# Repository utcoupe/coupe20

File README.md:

Coupe de France de Robotique 2020 - UTCoupe
=======
|master|devel|
|------|-----|
|  |  |

# Configuration

First clone the repo to your PC :
```
git clone git@github.com:utcoupe/coupe20.git
```

### Development environment configuration

An automated installation script is available. Go in the 'coupe20' folder and launch :
```
./scripts/install_utcoupe_setup.sh 
```

If it is your first installation, answer "y" to all questions.

### Compile the system

The whole system relies on ROS (http://www.ros.org/). Therefore you need to compile the system after having fetched it :
```
cd coupe20/ros_ws
catkin_make
```

### Source the system

Do not forget to source it !
If you are using bash : 
'''
source devel/setup.bash
'''

If you are using zsh : 
'''
source devel/setup.zsh
'''

You can add the source command with the absolute path to setup.bash in ~/.bashrc (or ~/.zshrc) to automate this process.

# Project guidelines

Here are some rules we follow to keep project consistency :

### Git

- Create git branches of format `namespace/package` for ROS packages (e.g. `ai/scheduler`, `memory/map`, etc).

### ROS packages

- Create ROS packages of format `namespace_package` (for alphabetic order sorting purposes)

- Create `topics`/`services`/`actions` in the format `/namespace/package/server_name` if they can be accessed by extern packages (WARNING : with `/` at the beginning to create an absolute name), `server_name` if they are only intern.

- Name definition files `.msg`/`.srv`/`.action` in PascalCase (e.g. `GetValues.srv`) and variables inside in lower case(format `var_name`).

### Python

- PEP8 : 4 indentation spaces (no tabs).

### Data

- Distance units in m, stored as `float32`.

- When describing a shape (circle, line, rectangle, point...), give the position relative to the center of the shape unless it is absolutely necessary.  For example, do not give the corner of a rectangle.

# Webclient

To install the webclient dependency :
```
cd webclient
npm install --only=prod
```

To launch the webclient :
```
npm start
```

Make sure the ROS node `rosbridge_server` starts right.

The webclient can be launched from the robot or a PC connected to the embedded computer (e.g. Raspberry or Lattepanda).

If the server is launched on the robot, go to `http://<ip_of_embedded_computer>:8080`.

Else, go to [http://localhost:8080](http://localhost:8080) and check if the client connects to the robot IP in the parameters.

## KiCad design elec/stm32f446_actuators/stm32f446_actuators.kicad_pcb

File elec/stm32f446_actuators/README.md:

# STM32F446re - Actuators

[Interactive BOM](http://htmlpreview.github.io/?https://github.com/utcoupe/coupe20/blob/elec/elec/stm32f446_actuators/bom/ibom.html)

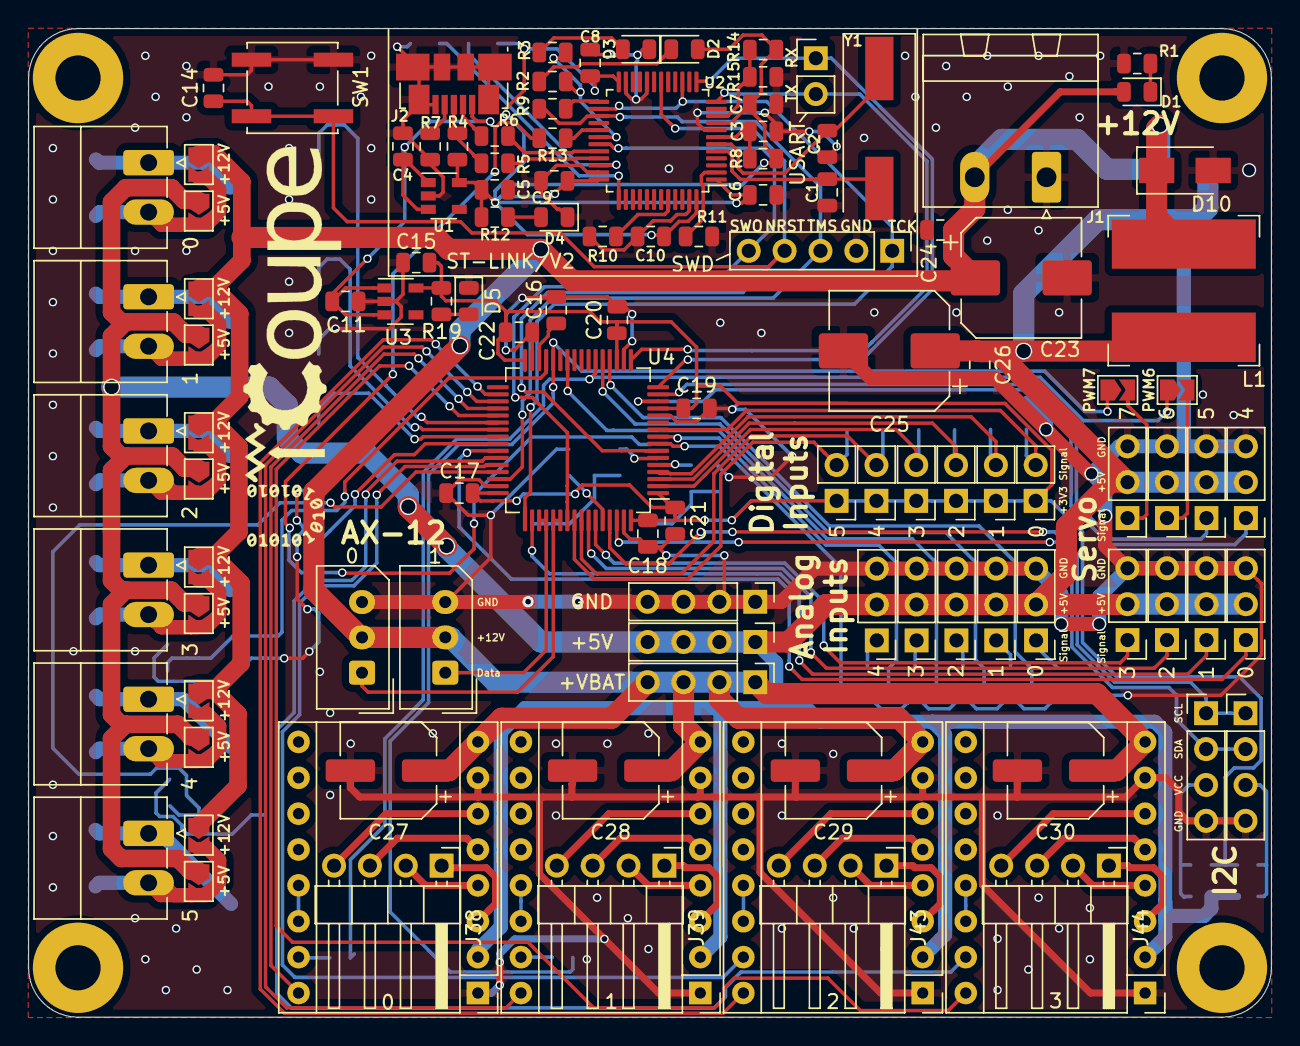
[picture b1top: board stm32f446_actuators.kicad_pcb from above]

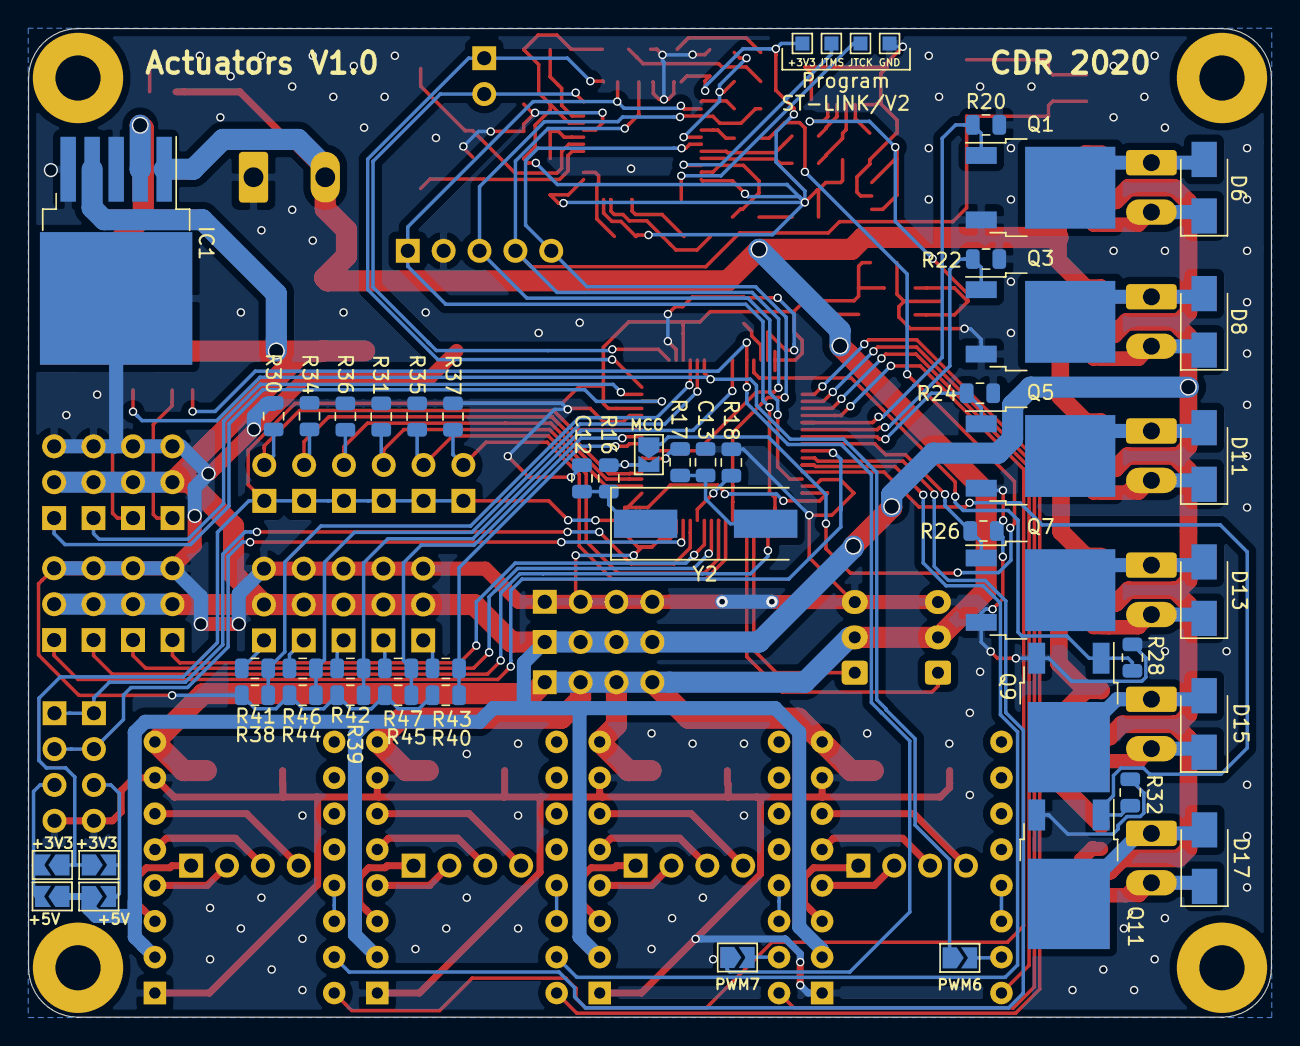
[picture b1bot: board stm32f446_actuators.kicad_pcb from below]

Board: 2 copper layers, 88.0 x 70.0 mm, 167 parts (52 on the bottom side), 119 nets.

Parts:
A1: 0; Pololu_Breakout-16_15.2x20.3mm
A2: 1; Pololu_Breakout-16_15.2x20.3mm
A3: 2; Pololu_Breakout-16_15.2x20.3mm
A4: 3; Pololu_Breakout-16_15.2x20.3mm
C1, C2: 20pF; C_0805_2012Metric
C3, C6, C7, C8, C9, C10, C14, C17, C18, C19, C20, C21, C22, C24, C26: 100nF; C_0805_2012Metric
C4, C5, C11, C15: 1uF; C_0805_2012Metric
C12, C13: 20pF[N/A]; C_0805_2012Metric
C16: 4.7uF(Low ESR); C_0805_2012Metric
C23, C25: 470uF; CP_Elec_8x10
C27, C28, C29, C30: 100uF; CP_Elec_6.3x7.7
D1: LED; LED_0805_2012Metric
D2: LED_G; LED_0805_2012Metric
D3, D4, D5: LED_R; LED_0805_2012Metric
D6, D8, D11, D13, D15, D17: B360A-13-F; D_SMA
D10: TSSA3U45; D_SMA
IC1: TS2596CM550_RNG; TO-263-5_TabPin6
J1: Conn_01x02; PhoenixContact_MSTBA_2,5_2-G-5,08_1x02_P5.08mm_Horizontal
J2: USB_B_Micro; USB_Micro-B_Molex_47346-0001
J3: USART; PinHeader_1x02_P2.54mm_Vertical
J4: SWD; PinHeader_1x05_P2.54mm_Vertical
J5: 0; Molex_SPOX_5267-03A_1x03_P2.50mm_Vertical
J6, J7: Conn_01x04; PinHeader_1x04_P2.54mm_Vertical
J8: 1; Molex_SPOX_5267-03A_1x03_P2.50mm_Vertical
J9: 0; PhoenixContact_MC_1,5_2-G-3.5_1x02_P3.50mm_Horizontal
J11: 1; PhoenixContact_MC_1,5_2-G-3.5_1x02_P3.50mm_Horizontal
J13: 2; PhoenixContact_MC_1,5_2-G-3.5_1x02_P3.50mm_Horizontal
J15: 3; PhoenixContact_MC_1,5_2-G-3.5_1x02_P3.50mm_Horizontal
J17, J40: 0; PinHeader_1x03_P2.54mm_Vertical
J18, J42: 4; PinHeader_1x03_P2.54mm_Vertical
J19: 4; PhoenixContact_MC_1,5_2-G-3.5_1x02_P3.50mm_Horizontal
J21: 0; PinHeader_1x02_P2.54mm_Vertical
J22: 3; PinHeader_1x02_P2.54mm_Vertical
J23, J45: 1; PinHeader_1x03_P2.54mm_Vertical
J24: 5; PinHeader_1x03_P2.54mm_Vertical
J25: 5; PhoenixContact_MC_1,5_2-G-3.5_1x02_P3.50mm_Horizontal
J27: 1; PinHeader_1x02_P2.54mm_Vertical
J28: 4; PinHeader_1x02_P2.54mm_Vertical
J29: +VBAT; PinHeader_1x04_P2.54mm_Vertical
J30, J41: 2; PinHeader_1x03_P2.54mm_Vertical
J31: 6; PinHeader_1x03_P2.54mm_Vertical
J32: 2; PinHeader_1x02_P2.54mm_Vertical
J33: 5; PinHeader_1x02_P2.54mm_Vertical
J34: +5V; PinHeader_1x04_P2.54mm_Vertical
J35: GND; PinHeader_1x04_P2.54mm_Vertical
J36, J46: 3; PinHeader_1x03_P2.54mm_Vertical
J37: 7; PinHeader_1x03_P2.54mm_Vertical
J38, J39, J43, J44: Conn_01x04; PinHeader_1x04_P2.54mm_Horizontal
JP1: MCO; SolderJumper-2_P1.3mm_Open_TrianglePad1.0x1.5mm
JP2, JP3: +3V3; SolderJumper-2_P1.3mm_Open_TrianglePad1.0x1.5mm
JP4, JP5, JP8, JP12, JP16, JP22, JP30, JP36: +5V; SolderJumper-2_P1.3mm_Open_TrianglePad1.0x1.5mm
JP6, JP10, JP14, JP18, JP26, JP34: +12V; SolderJumper-2_P1.3mm_Open_TrianglePad1.0x1.5mm
JP40, JP48: PWM6; SolderJumper-2_P1.3mm_Open_TrianglePad1.0x1.5mm
JP45, JP49: PWM7; SolderJumper-2_P1.3mm_Open_TrianglePad1.0x1.5mm
L1: 33uH; L_Bourns-SRN1060
Q1, Q3, Q5, Q7, Q9, Q11: IRLZ44N; TO-252-2
R1: 560; R_0805_2012Metric
R2, R3: 220; R_0805_2012Metric
R4: 1k5; R_0805_2012Metric
R5, R6: 22; R_0805_2012Metric
R7, R8, R10: 100k; R_0805_2012Metric
R9, R13: 100; R_0805_2012Metric
R11, R18, R20, R22, R24, R26, R28, R30, R31, R32, R34, R35, R36, R37: 10k; R_0805_2012Metric
R12, R19: 56; R_0805_2012Metric
R14, R15: 4k7; R_0805_2012Metric
R16, R17: [N/A]; R_0805_2012Metric
R38, R39, R40, R41, R42, R43, R44, R45, R46, R47: R; R_0805_2012Metric
SW1: RESET; SW_Push_1P1T_NO_CK_KSC6xxJ
TP1: +3V3; TestPoint_Pad_1.0x1.0mm
TP2: JTMS; TestPoint_Pad_1.0x1.0mm
TP3: JTCK; TestPoint_Pad_1.0x1.0mm
TP4: GND; TestPoint_Pad_1.0x1.0mm
U1, U3: MIC5504-3.3YM5; SOT-23-5
U2: STM32F103CBTx; LQFP-48_7x7mm_P0.5mm
U4: STM32F446RETx; LQFP-64_10x10mm_P0.5mm
Y1: 8MHz(12pF); Crystal_SMD_HC49-SD
Y2: 8MHz(16pF)[N/A]; Crystal_SMD_HC49-SD

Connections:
+3V3: C15.1, C17.1, C18.1, C19.1, C20.1, C21.1, C22.1, J21.1, J22.1, J27.1, J28.1, J32.1, J33.1, JP2.1, JP3.1, R19.1, U3.5, U4.1, U4.13, U4.19, U4.32, U4.48, U4.64
+5V: A1.2, A2.2, A3.2, A4.2, C25.1, C26.1, IC1.4, J17.2, J18.2, J23.2, J24.2, J30.2, J31.2, J34.1, J34.2, J34.3, J34.4, J36.2, J37.2, J40.2, J41.2, J42.2, J45.2, J46.2, JP4.1, JP5.1, JP8.1, JP12.1, JP16.1, JP22.1, JP30.1, JP36.1, L1.2
+12V: A1.8, A2.8, A3.8, A4.8, C23.1, C24.1, C27.1, C28.1, C29.1, C30.1, D1.2, IC1.1, J1.2, J5.2, J8.2, J29.1, J29.2, J29.3, J29.4, JP6.1, JP10.1, JP14.1, JP18.1, JP26.1, JP34.1
/Actuators/AnalogIn0: R38.1, R41.1, U4.20
/Actuators/AnalogIn1: R44.1, R46.1, U4.21
/Actuators/AnalogIn2: R39.1, R42.1, U4.26
/Actuators/AnalogIn3: R45.1, R47.1, U4.9
/Actuators/AnalogIn4: R40.1, R43.1, U4.8
/Actuators/DigitalIn0: J21.2, R30.1, U4.10
/Actuators/DigitalIn1: J27.2, R34.1, U4.4
/Actuators/DigitalIn2: J32.2, R36.1, U4.3
/Actuators/DigitalIn3: J22.2, R31.1, U4.2
/Actuators/DigitalIn4: J28.2, R35.1, U4.57
/Actuators/DigitalIn5: J33.2, R37.1, U4.56
/Actuators/DigitalOut0: A1.16, U4.36
/Actuators/DigitalOut1: A2.16, U4.35
/Actuators/DigitalOut2: A3.16, U4.34
/Actuators/DigitalOut3: A4.16, U4.37
/Actuators/DigitalOut4: Q11.1, R32.1, U4.45
/Actuators/PWM0: J17.1, U4.42
/Actuators/PWM1: J23.1, U4.50
/Actuators/PWM2: J30.1, U4.58
/Actuators/PWM3: J36.1, U4.59
/Actuators/PWM4: J18.1, U4.14
/Actuators/PWM5: J24.1, U4.15
/Actuators/PWM6: JP40.1, JP48.1, U4.22
/Actuators/PWM7: JP45.1, JP49.1, U4.28
/Actuators/PWM8: A3.15, U4.44
/Actuators/PWM9: A4.15, U4.43
/Actuators/PWM10: Q1.1, R20.1, U4.38
/Actuators/PWM11: Q3.1, R22.1, U4.39
/Actuators/PWM12: Q5.1, R24.1, U4.40
/Actuators/PWM13: Q7.1, R26.1, U4.41
/Actuators/PWM14: Q9.1, R28.1, U4.29
/Actuators/RX3: J8.1, U4.51, U4.52
/Actuators/RX5: J5.1, U4.53, U4.54
/STM32F446RE6/I2C1_SCL: J6.1, J7.1, U4.61
/STM32F446RE6/I2C1_SDA: J6.2, J7.2, U4.62
/STM32F446RE6/MCO: JP1.1, R13.2
/STM32F446RE6/NRST: C14.1, J4.4, SW1.2, U2.18, U4.7
/STM32F446RE6/PH0: JP1.2, R16.1, U4.5
/STM32F446RE6/PH1: R17.1, U4.6
/STM32F446RE6/SWO: J4.5, U2.31, U4.55
/STM32F446RE6/TCK: J4.1, U2.15, U2.26, U4.49
/STM32F446RE6/TMS: J4.3, R9.2, U2.27, U4.46
/ST_Link_v2/AIN_1: R14.2, R15.1, U2.10
/ST_Link_v2/BOOT0: R10.1, U2.44
/ST_Link_v2/LED_STLINK: R2.2, R3.2, U2.30
/ST_Link_v2/OSC_IN: C1.1, U2.5, Y1.2
/ST_Link_v2/OSC_OUT: C2.2, U2.6, Y1.1
/ST_Link_v2/STLINK_3V3: C5.1, C6.1, C7.1, C8.1, C9.1, C10.1, D2.2, R4.1, R8.1, R12.1, R14.1, TP1.1, U1.5, U2.1, U2.9, U2.24, U2.36, U2.48
/ST_Link_v2/STLK_RX: J3.1, U2.13, U4.16
/ST_Link_v2/STLK_TX: J3.2, U2.12, U4.17
/ST_Link_v2/STM_JTCK: TP3.1, U2.37
/ST_Link_v2/STM_JTMS: TP2.1, U2.34
/ST_Link_v2/STM_RESET: C3.1, R8.2, U2.7
/ST_Link_v2/T_SWDIO_IN: R9.1, U2.25
/ST_Link_v2/USB_DM: R6.1, U2.32
/ST_Link_v2/USB_DP: R5.1, U2.33
GND: A1.1, A1.7, A2.1, A2.7, A3.1, A3.7, A4.1, A4.7, C1.2, C2.1, C3.2, C4.2, C5.2, C6.2, C7.2, C8.2, C9.2, C10.2, C11.2, C12.2, C13.2, C14.2, C15.2, C16.2, C17.2, C18.2, C19.2, C20.2, C21.2, C22.2, C23.2, C24.2, C25.2, C26.2, C27.2, C28.2, C29.2, C30.2, D3.1, D4.1, D5.1, D10.2, IC1.3, IC1.5, IC1.6, J1.1, J2.5, J2.6, J4.2, J5.3, J6.4, J7.4, J8.3, J17.3, J18.3, J23.3, J24.3, J30.3, J31.3, J35.1, J35.2, J35.3, J35.4, J36.3, J37.3, J40.3, J41.3, J42.3, J45.3, J46.3, Q1.3, Q3.3, Q5.3, Q7.3, Q9.3, Q11.3, R1.2, R7.1, R10.2, R11.2, R15.2, R18.2, R20.2, R22.2, R24.2, R26.2, R28.2, R30.2, R31.2, R32.2, R34.2, R35.2, R36.2, R37.2, R38.2, R39.2, R40.2, R44.2, R45.2, SW1.1, TP4.1, U1.2, U2.8, U2.20, U2.23, U2.35, U2.47, U3.2, U4.12, U4.18, U4.31, U4.47, U4.63
unnamed: A1.3, J38.1
unnamed: A1.4, J38.2
unnamed: A1.5, J38.3
unnamed: A1.6, J38.4
unnamed: A1.13, A1.14
unnamed: A1.15, JP48.2
unnamed: A2.3, J39.1
unnamed: A2.4, J39.2
unnamed: A2.5, J39.3
unnamed: A2.6, J39.4
unnamed: A2.13, A2.14
unnamed: A2.15, JP49.2
unnamed: A3.3, J43.1
unnamed: A3.4, J43.2
unnamed: A3.5, J43.3
unnamed: A3.6, J43.4
unnamed: A3.13, A3.14
unnamed: A4.3, J44.1
unnamed: A4.4, J44.2
unnamed: A4.5, J44.3
unnamed: A4.6, J44.4
unnamed: A4.13, A4.14
unnamed: C12.1, R16.2, Y2.1
unnamed: C13.1, R17.2, Y2.2
unnamed: C16.1, U4.30
unnamed: D1.1, R1.1
unnamed: D2.1, R2.1
unnamed: D3.2, R3.1
unnamed: D4.2, R12.2
unnamed: D5.2, R19.2
unnamed: D6.1, J9.2, JP6.2, JP8.2
unnamed: D6.2, J9.1, Q1.2
unnamed: D8.1, J11.2, JP10.2, JP12.2
unnamed: D8.2, J11.1, Q3.2
unnamed: D10.1, IC1.2, L1.1
unnamed: D11.1, J13.2, JP14.2, JP16.2
unnamed: D11.2, J13.1, Q5.2
unnamed: D13.1, J15.2, JP18.2, JP22.2
unnamed: D13.2, J15.1, Q7.2
unnamed: D15.1, J19.2, JP26.2, JP30.2
unnamed: D15.2, J19.1, Q9.2
unnamed: D17.1, J25.2, JP34.2, JP36.2
unnamed: D17.2, J25.1, Q11.2
unnamed: J2.2, R6.2
unnamed: J2.3, R4.2, R5.2
unnamed: J2.4, R7.2
unnamed: J6.3, JP2.2, JP4.2
unnamed: J7.3, JP3.2, JP5.2
unnamed: J31.1, JP40.2
unnamed: J37.1, JP45.2
unnamed: J40.1, R41.2
unnamed: J41.1, R42.2
unnamed: J42.1, R43.2
unnamed: J45.1, R46.2
unnamed: J46.1, R47.2
unnamed: R11.1, U2.2
unnamed: R13.1, U2.29
unnamed: R18.1, U4.60
VBUS: C4.1, C11.1, J2.1, U1.1, U1.3, U3.1, U3.3

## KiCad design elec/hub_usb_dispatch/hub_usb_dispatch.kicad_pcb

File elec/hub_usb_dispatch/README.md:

# USB Hub - Power Dispatch

[Interactive BOM](http://htmlpreview.github.io/?https://github.com/utcoupe/coupe20/blob/elec/elec/hub_usb_dispatch/bom/ibom.html)

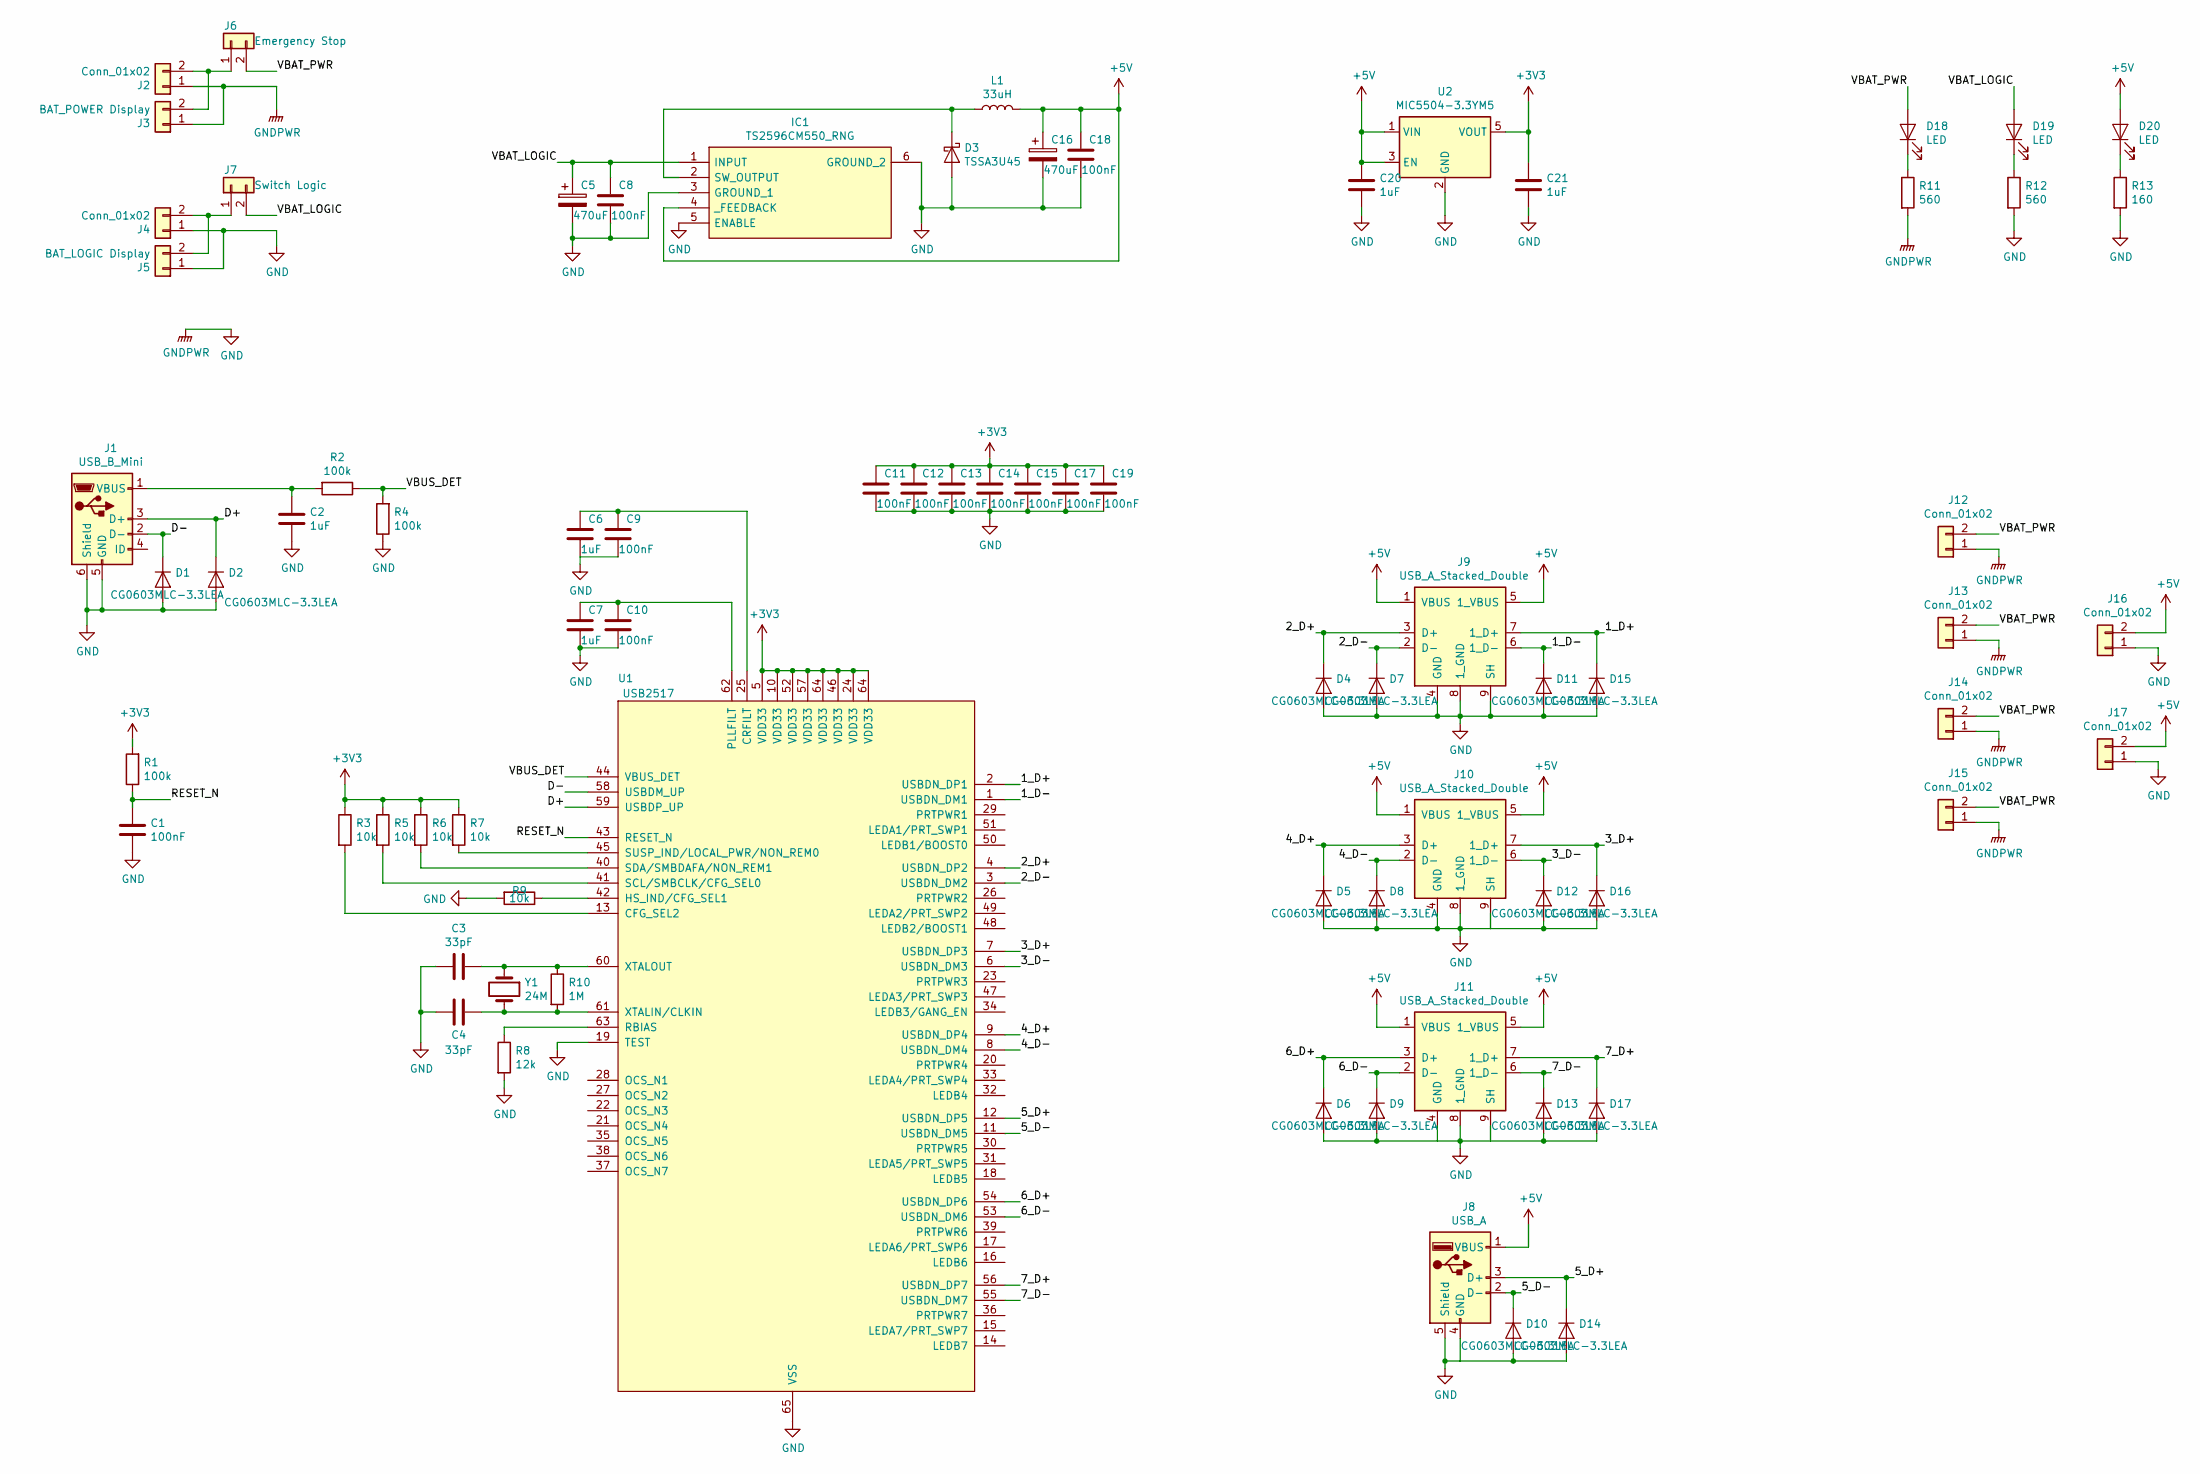
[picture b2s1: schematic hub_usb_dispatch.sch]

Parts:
C1, C8, C9, C10, C11, C12, C13, C14, C15, C17, C18, C19: 100nF; C_0805_2012Metric
C2, C6, C7, C20, C21: 1uF; C_0805_2012Metric
C3, C4: 33pF; C_0805_2012Metric
C5, C16: 470uF; CP_Elec_8x10
D1, D2, D4, D5, D6, D7, D8, D9, D10, D11, D12, D13, D14, D15, D16, D17: CG0603MLC-3.3LEA; D_0603_1608Metric
D3: TSSA3U45; D_SMA
D18, D19, D20: LED; LED_0805_2012Metric
IC1: TS2596CM550_RNG; TO-263-5_TabPin6; Manufacturer_Part_Number TS2596CM550 RNG; Mouser Part Number 821-TS2596CM550RNG
J1: USB_B_Mini; USB_Mini-B_Lumberg_2486_01_Horizontal
J2, J4, J12, J13, J14, J15: Conn_01x02; PhoenixContact_MSTBA_2,5_2-G-5,08_1x02_P5.08mm_Horizontal
J3: BAT_POWER Display; Headers-Wire_Housings_HEADER_2POS_HE14
J5: BAT_LOGIC Display; Headers-Wire_Housings_HEADER_2POS_HE14
J6: Emergency Stop; PhoenixContact_MSTBVA_2,5_2-G-5,08_1x02_P5.08mm_Vertical
J7: Switch Logic; PhoenixContact_MSTBVA_2,5_2-G-5,08_1x02_P5.08mm_Vertical
J8: USB_A; USB_A_Stewart_SS-52100-001_Horizontal
J9, J10, J11: USB_A_Stacked_Double; USB_A_Wuerth_61400826021_Horizontal_Stacked
J16, J17: Conn_01x02; PhoenixContact_MC_1,5_2-G-3.5_1x02_P3.50mm_Horizontal
L1: 33uH; L_Bourns-SRN1060
R1, R2, R4: 100k; R_0805_2012Metric
R3, R5, R6, R7, R9: 10k; R_0805_2012Metric
R8: 12k; R_0805_2012Metric
R10: 1M; R_0805_2012Metric
R11, R12: 560; R_0805_2012Metric
R13: 160; R_0805_2012Metric
U1: USB2517; QFN-64-1EP_9x9mm_P0.5mm_EP4.7x4.7mm_ThermalVias
U2: MIC5504-3.3YM5; SOT-23-5
Y1: 24M; Crystal_SMD_HC49-SD

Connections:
+3V3: C11.1, C12.1, C13.1, C14.1, C15.1, C17.1, C19.1, C21.1, R1.2, R3.1, R5.1, R6.1, R7.1, U1.5 (VDD33), U1.10 (VDD33), U1.24 (VDD33), U1.46 (VDD33), U1.52 (VDD33), U1.57 (VDD33), U1.64 (VDD33), U2.5 (VOUT)
+5V: C16.1, C18.1, C20.1, D20.2 (A), IC1.4 (_FEEDBACK), J8.1 (VBUS), J9.1 (VBUS), J9.5 (1_VBUS), J10.1 (VBUS), J10.5 (1_VBUS), J11.1 (VBUS), J11.5 (1_VBUS), J16.2, J17.2, L1.2, U2.1 (VIN), U2.3 (EN)
/1_D+: D15.1 (K), J9.7 (1_D+), U1.2 (USBDN_DP1)
/1_D-: D11.1 (K), J9.6 (1_D-), U1.1 (USBDN_DM1)
/2_D+: D4.1 (K), J9.3 (D+), U1.4 (USBDN_DP2)
/2_D-: D7.1 (K), J9.2 (D-), U1.3 (USBDN_DM2)
/3_D+: D16.1 (K), J10.7 (1_D+), U1.7 (USBDN_DP3)
/3_D-: D12.1 (K), J10.6 (1_D-), U1.6 (USBDN_DM3)
/4_D+: D5.1 (K), J10.3 (D+), U1.9 (USBDN_DP4)
/4_D-: D8.1 (K), J10.2 (D-), U1.8 (USBDN_DM4)
/5_D+: D14.1 (K), J8.3 (D+), U1.12 (USBDN_DP5)
/5_D-: D10.1 (K), J8.2 (D-), U1.11 (USBDN_DM5)
/6_D+: D6.1 (K), J11.3 (D+), U1.54 (USBDN_DP6)
/6_D-: D9.1 (K), J11.2 (D-), U1.53 (USBDN_DM6)
/7_D+: D17.1 (K), J11.7 (1_D+), U1.56 (USBDN_DP7)
/7_D-: D13.1 (K), J11.6 (1_D-), U1.55 (USBDN_DM7)
/D+: D2.1 (K), J1.3 (D+), U1.59 (USBDP_UP)
/D-: D1.1 (K), J1.2 (D-), U1.58 (USBDM_UP)
/RESET_N: C1.1, R1.1, U1.43 (RESET_N)
/VBAT_LOGIC: C5.1, C8.1, D19.2 (A), IC1.1 (INPUT), J7.2
/VBAT_PWR: D18.2 (A), J6.2, J12.2, J13.2, J14.2, J15.2
/VBUS_DET: R2.1, R4.2, U1.44 (VBUS_DET)
GND: C1.2, C2.2, C3.2, C4.2, C5.2, C6.2, C7.2, C8.2, C9.2, C10.2, C11.2, C12.2, C13.2, C14.2, C15.2, C16.2, C17.2, C18.2, C19.2, C20.2, C21.2, D1.2 (A), D2.2 (A), D3.2 (A), D4.2 (A), D5.2 (A), D6.2 (A), D7.2 (A), D8.2 (A), D9.2 (A), D10.2 (A), D11.2 (A), D12.2 (A), D13.2 (A), D14.2 (A), D15.2 (A), D16.2 (A), D17.2 (A), IC1.3 (GROUND_1), IC1.5 (ENABLE), IC1.6 (GROUND_2), J1.5 (GND), J1.6 (Shield), J2.1, J3.1, J4.1, J5.1, J8.4 (GND), J8.5 (Shield), J9.4 (GND), J9.8 (1_GND), J9.9 (SH), J10.4 (GND), J10.8 (1_GND), J10.9 (SH), J11.4 (GND), J11.8 (1_GND), J11.9 (SH), J12.1, J13.1, J14.1, J15.1, J16.1, J17.1, R4.1, R8.2, R9.2, R11.2, R12.2, R13.2, U1.19 (TEST), U1.65 (VSS), U2.2 (GND)
unnamed: C2.1, J1.1 (VBUS), R2.2
unnamed: C3.1, R10.1, U1.60 (XTALOUT), Y1.1
unnamed: C4.1, R10.2, U1.61 (XTALIN/CLKIN), Y1.2
unnamed: C6.1, C9.1, U1.25 (CRFILT)
unnamed: C7.1, C10.1, U1.62 (PLLFILT)
unnamed: D3.1 (K), IC1.2 (SW_OUTPUT), L1.1
unnamed: D18.1 (K), R11.1
unnamed: D19.1 (K), R12.1
unnamed: D20.1 (K), R13.1
unnamed: J2.2, J3.2, J6.1
unnamed: J4.2, J5.2, J7.1
unnamed: R3.2, U1.13 (CFG_SEL2)
unnamed: R5.2, U1.41 (SCL/SMBCLK/CFG_SEL0)
unnamed: R6.2, U1.40 (SDA/SMBDAFA/NON_REM1)
unnamed: R7.2, U1.45 (SUSP_IND/LOCAL_PWR/NON_REM0)
unnamed: R8.1, U1.63 (RBIAS)
unnamed: R9.1, U1.42 (HS_IND/CFG_SEL1)

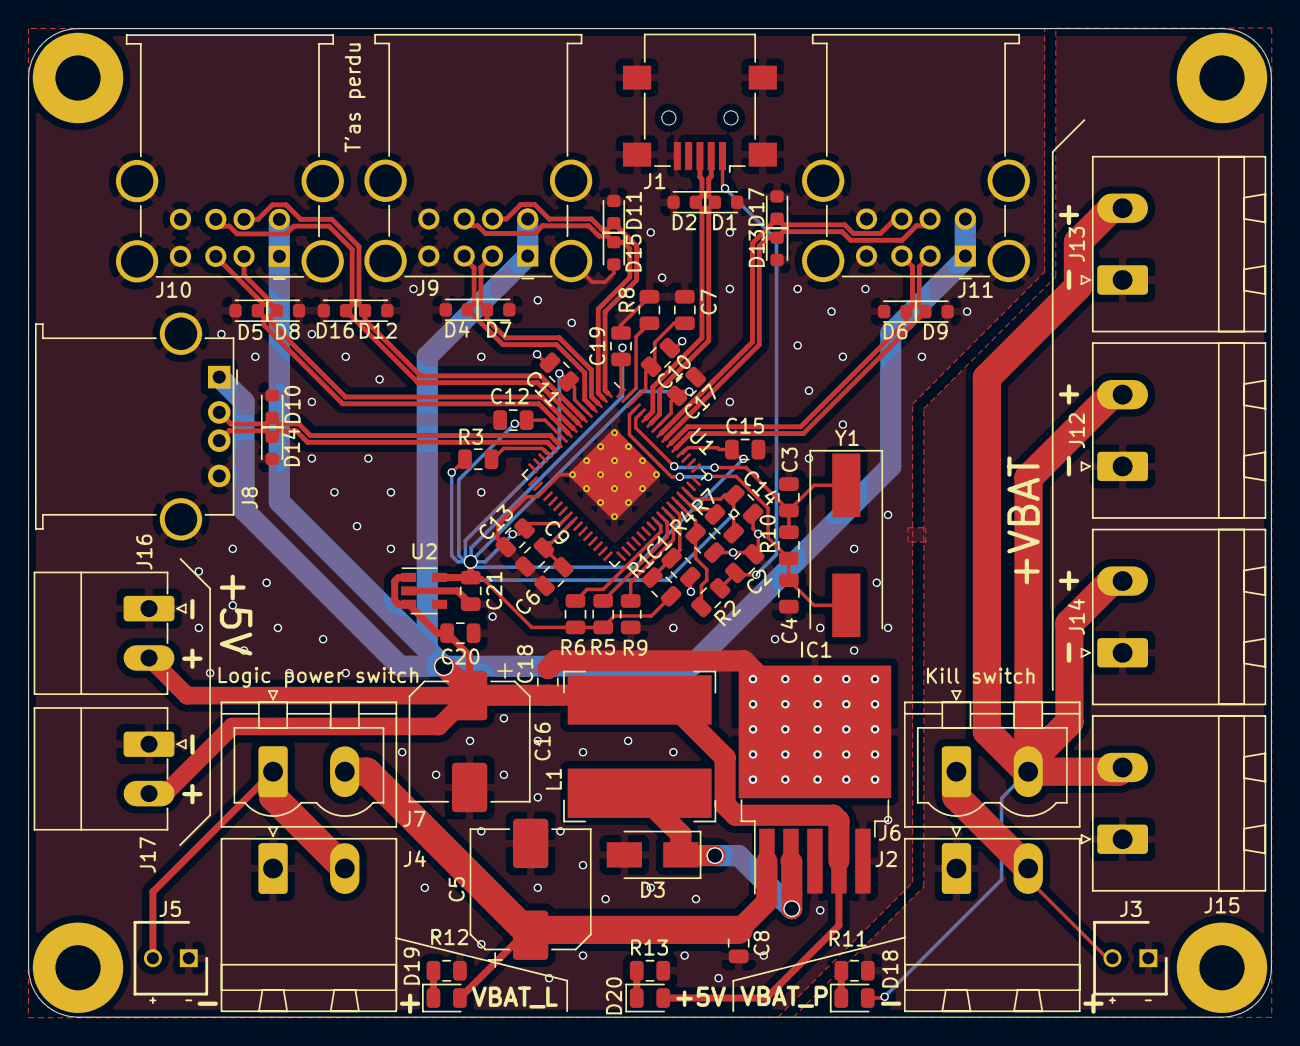
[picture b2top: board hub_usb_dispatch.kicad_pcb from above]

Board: 2 copper layers, 88.0 x 70.0 mm, 76 parts (0 on the bottom side), 40 nets.

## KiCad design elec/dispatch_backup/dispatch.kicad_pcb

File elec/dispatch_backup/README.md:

# Power Dispatch

[Interactive BOM](http://htmlpreview.github.io/?https://github.com/utcoupe/coupe20/blob/elec/elec/dispatch_backup/bom/ibom.html)

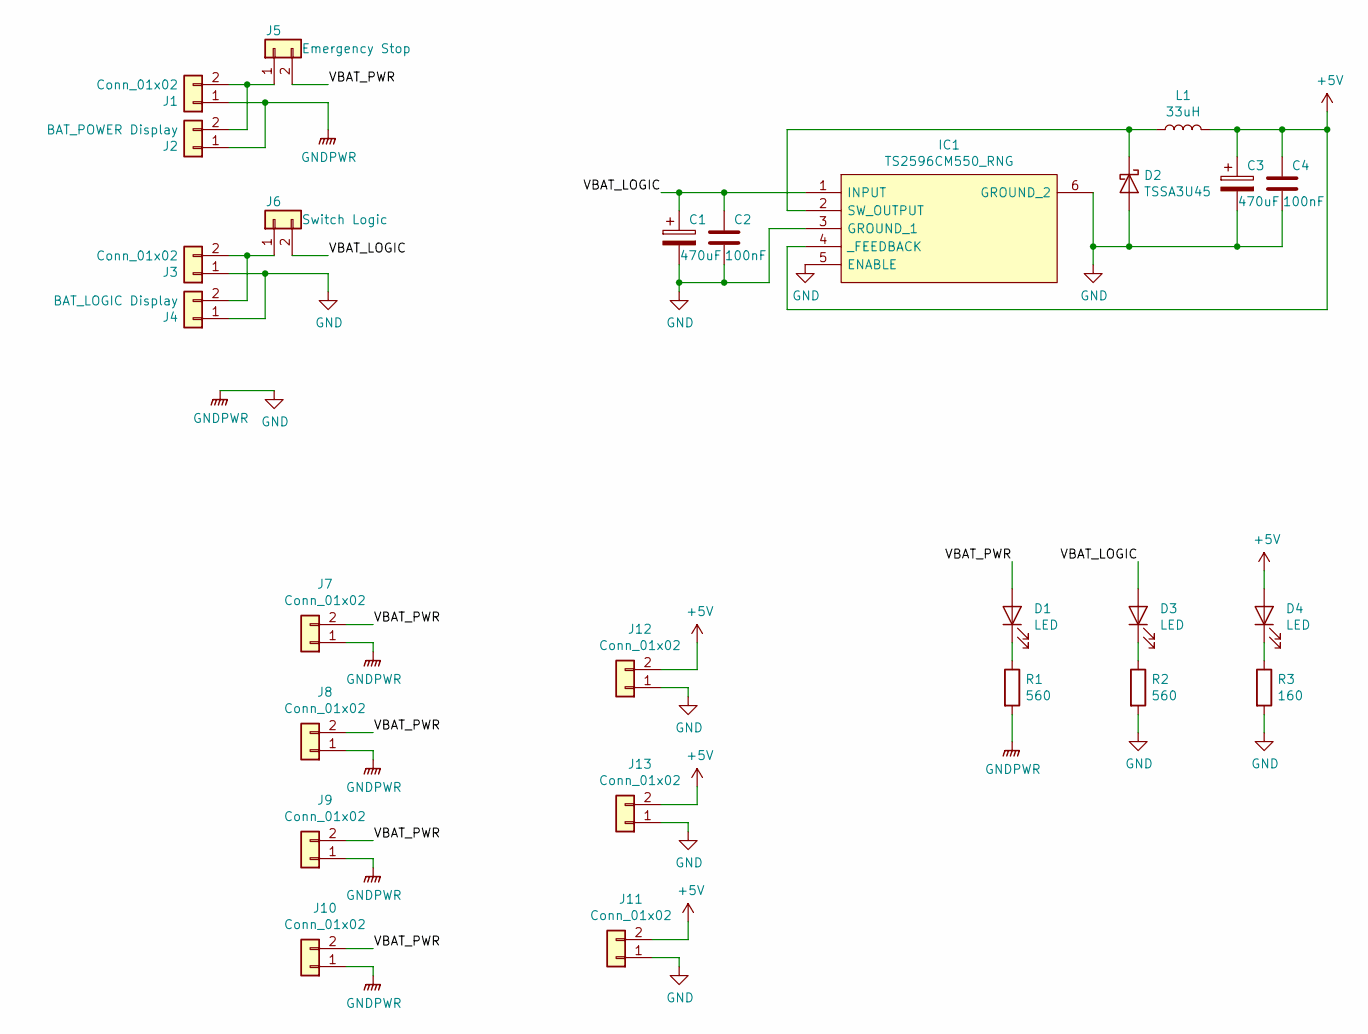
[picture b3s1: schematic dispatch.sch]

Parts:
C1, C3: 470uF; CP_Elec_8x10
C2, C4: 100nF; C_0805_2012Metric
D1, D3, D4: LED; LED_0805_2012Metric
D2: TSSA3U45; D_SMA
IC1: TS2596CM550_RNG; TO-263-5_TabPin6; Manufacturer_Part_Number TS2596CM550 RNG; Mouser Part Number 821-TS2596CM550RNG
J1, J3, J7, J8, J9, J10: Conn_01x02; PhoenixContact_MSTBA_2,5_2-G-5,08_1x02_P5.08mm_Horizontal
J2: BAT_POWER Display; Headers-Wire_Housings_HEADER_2POS_HE14
J4: BAT_LOGIC Display; Headers-Wire_Housings_HEADER_2POS_HE14
J5: Emergency Stop; PhoenixContact_MSTBVA_2,5_2-G-5,08_1x02_P5.08mm_Vertical
J6: Switch Logic; PhoenixContact_MSTBVA_2,5_2-G-5,08_1x02_P5.08mm_Vertical
J11, J12, J13: Conn_01x02; PhoenixContact_MC_1,5_2-G-3.5_1x02_P3.50mm_Horizontal
L1: 33uH; L_Bourns-SRN1060
R1, R2: 560; R_0805_2012Metric
R3: 160; R_0805_2012Metric

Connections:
+5V: C3.1, C4.1, D4.2 (A), IC1.4 (_FEEDBACK), J11.2, J12.2, J13.2, L1.2
/VBAT_LOGIC: C1.1, C2.1, D3.2 (A), IC1.1 (INPUT), J6.2
/VBAT_PWR: D1.2 (A), J5.2, J7.2, J8.2, J9.2, J10.2
GND: C1.2, C2.2, C3.2, C4.2, D2.2 (A), IC1.3 (GROUND_1), IC1.5 (ENABLE), IC1.6 (GROUND_2), J1.1, J2.1, J3.1, J4.1, J7.1, J8.1, J9.1, J10.1, J11.1, J12.1, J13.1, R1.2, R2.2, R3.2
unnamed: D1.1 (K), R1.1
unnamed: D2.1 (K), IC1.2 (SW_OUTPUT), L1.1
unnamed: D3.1 (K), R2.1
unnamed: D4.1 (K), R3.1
unnamed: J1.2, J2.2, J5.1
unnamed: J3.2, J4.2, J6.1

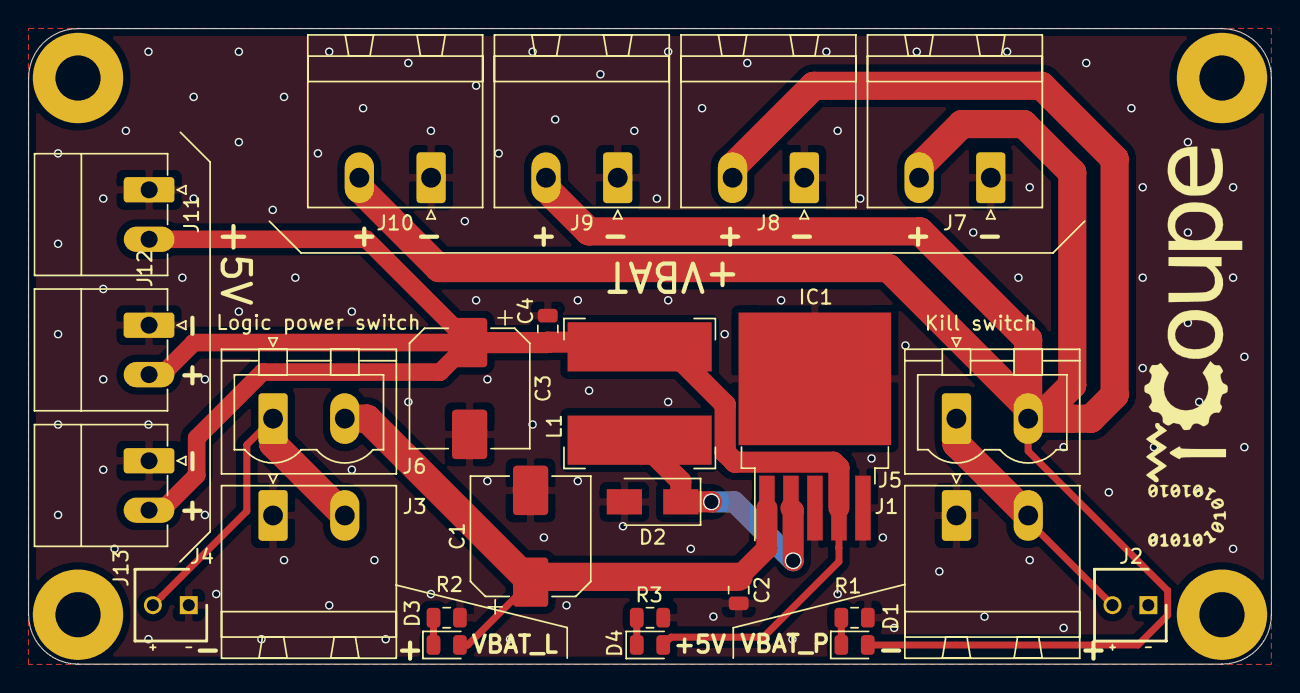
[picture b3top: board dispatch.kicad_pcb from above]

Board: 2 copper layers, 88.0 x 45.0 mm, 26 parts (0 on the bottom side), 10 nets.

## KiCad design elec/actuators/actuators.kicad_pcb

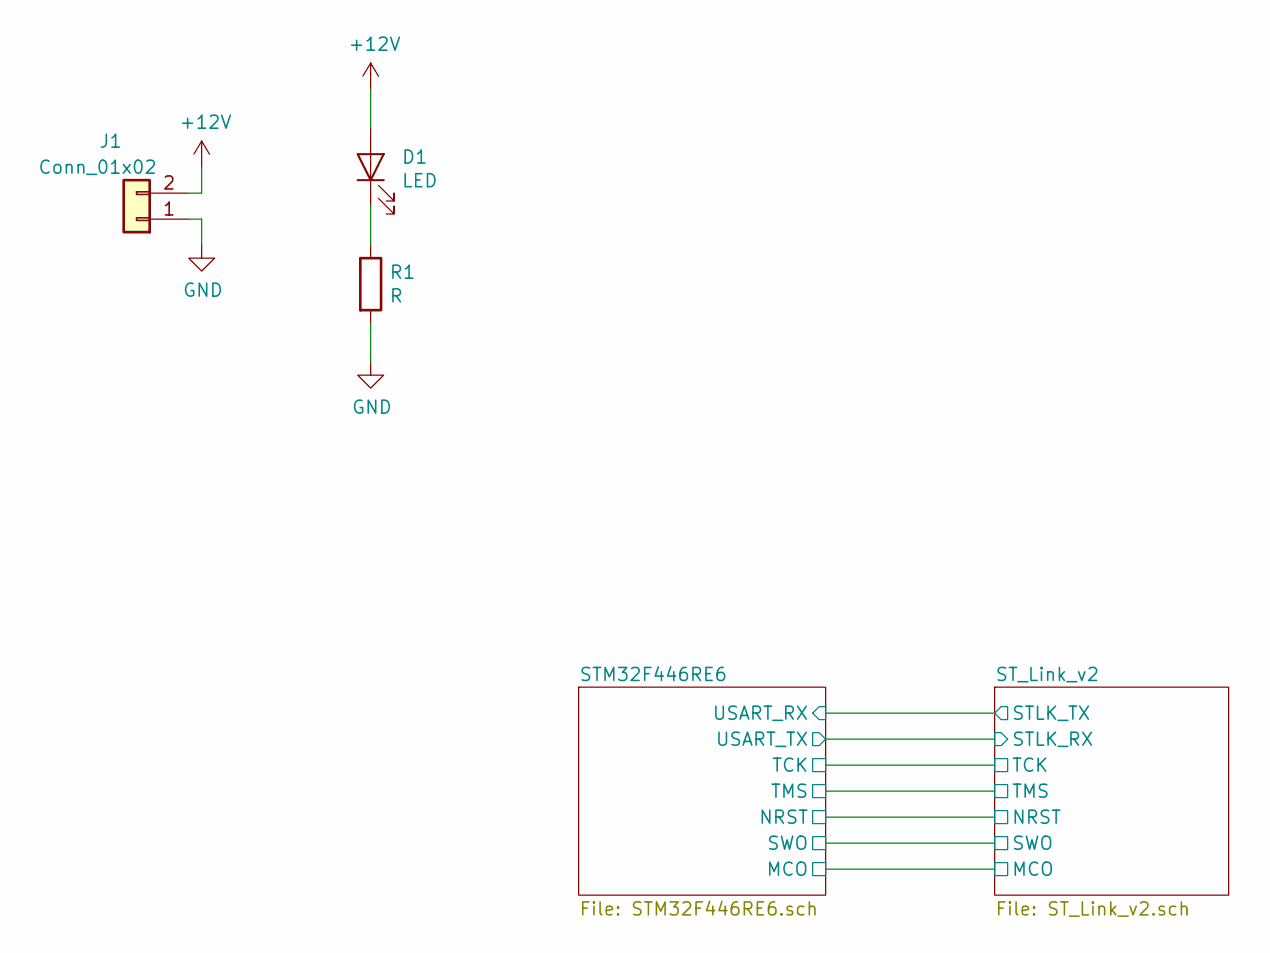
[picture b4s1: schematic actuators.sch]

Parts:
D1: LED; LED_0805_2012Metric
J1: Conn_01x02; PhoenixContact_MSTBA_2,5_2-G-5,08_1x02_P5.08mm_Horizontal
R1: R; R_0805_2012Metric

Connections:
+12V: D1.2 (A), J1.2
unnamed: D1.1 (K), R1.1
